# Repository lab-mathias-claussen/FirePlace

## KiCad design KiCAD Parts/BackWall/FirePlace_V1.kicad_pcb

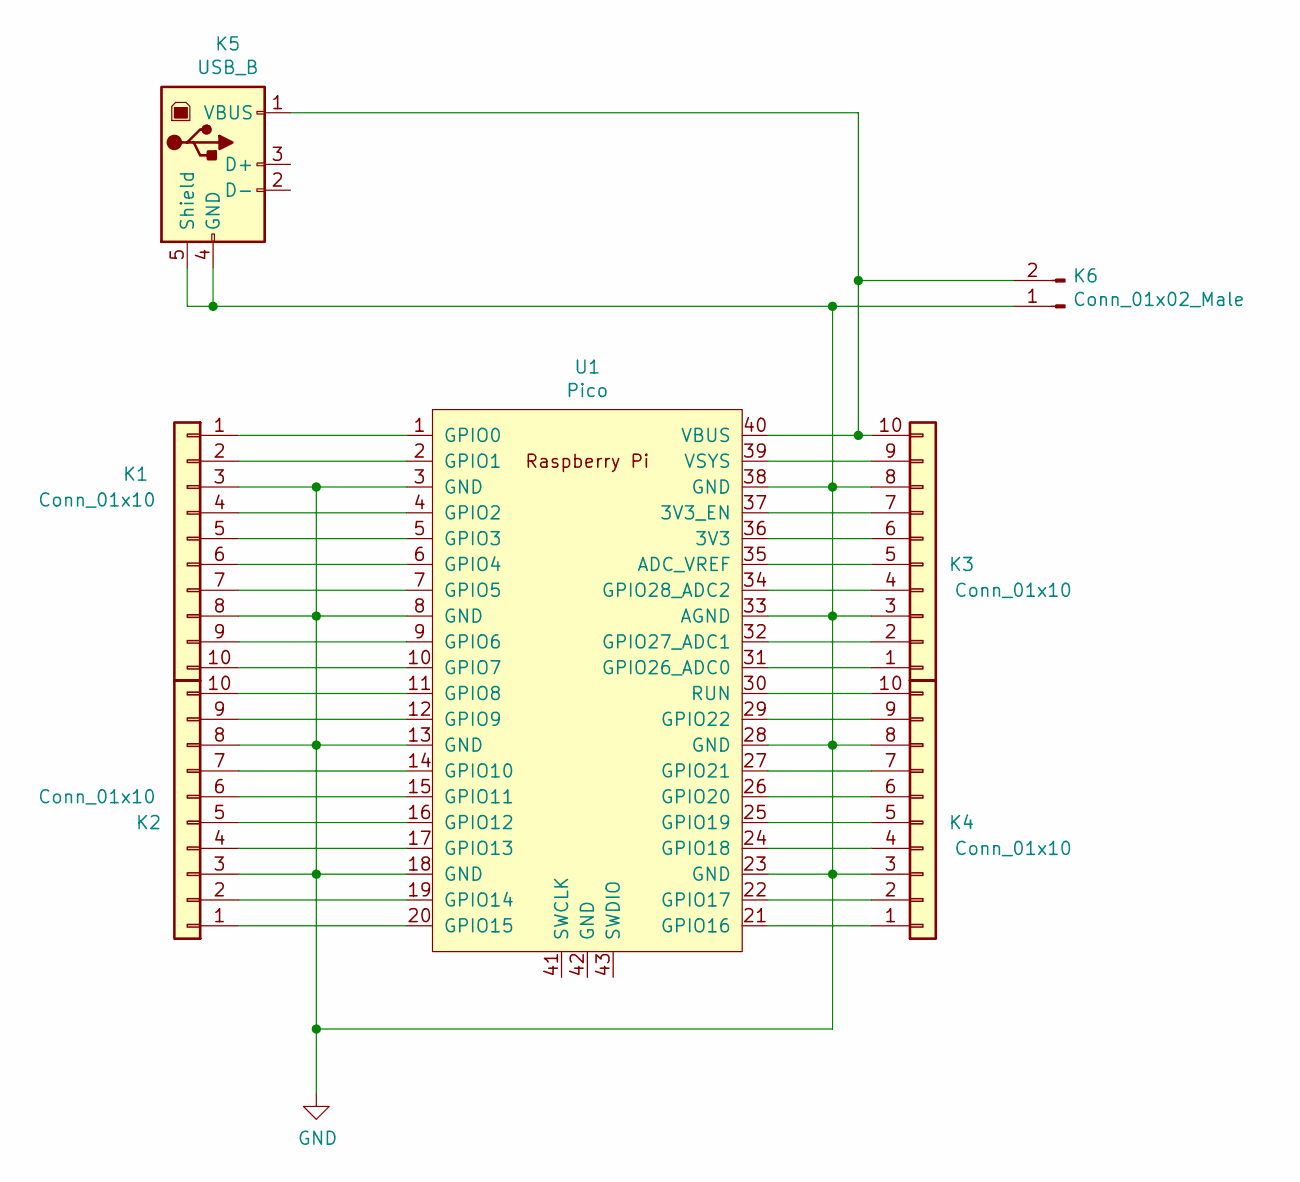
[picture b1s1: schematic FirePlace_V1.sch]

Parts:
K1, K2, K3, K4: Conn_01x10; PinHeader_1x10_P2.54mm_Vertical
K5: USB_B; USB_B_Lumberg_2411_02_Horizontal
K6: Conn_01x02_Male; PinHeader_1x02_P2.54mm_Vertical
U1: Pico; RPi_Pico_SMD_TH

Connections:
GND: K1.3, K1.8, K2.3, K2.8, K3.3, K3.8, K4.3, K4.8, K5.4 (GND), K5.5 (Shield), K6.1, U1.3 (GND), U1.8 (GND), U1.13 (GND), U1.18 (GND), U1.23 (GND), U1.28 (GND), U1.33 (AGND), U1.38 (GND)
unnamed: K1.1, U1.1 (GPIO0)
unnamed: K1.2, U1.2 (GPIO1)
unnamed: K1.4, U1.4 (GPIO2)
unnamed: K1.5, U1.5 (GPIO3)
unnamed: K1.6, U1.6 (GPIO4)
unnamed: K1.7, U1.7 (GPIO5)
unnamed: K1.9, U1.9 (GPIO6)
unnamed: K1.10, U1.10 (GPIO7)
unnamed: K2.1, U1.20 (GPIO15)
unnamed: K2.2, U1.19 (GPIO14)
unnamed: K2.4, U1.17 (GPIO13)
unnamed: K2.5, U1.16 (GPIO12)
unnamed: K2.6, U1.15 (GPIO11)
unnamed: K2.7, U1.14 (GPIO10)
unnamed: K2.9, U1.12 (GPIO9)
unnamed: K2.10, U1.11 (GPIO8)
unnamed: K3.1, U1.31 (GPIO26_ADC0)
unnamed: K3.2, U1.32 (GPIO27_ADC1)
unnamed: K3.4, U1.34 (GPIO28_ADC2)
unnamed: K3.5, U1.35 (ADC_VREF)
unnamed: K3.6, U1.36 (3V3)
unnamed: K3.7, U1.37 (3V3_EN)
unnamed: K3.9, U1.39 (VSYS)
unnamed: K3.10, K5.1 (VBUS), K6.2, U1.40 (VBUS)
unnamed: K4.1, U1.21 (GPIO16)
unnamed: K4.2, U1.22 (GPIO17)
unnamed: K4.4, U1.24 (GPIO18)
unnamed: K4.5, U1.25 (GPIO19)
unnamed: K4.6, U1.26 (GPIO20)
unnamed: K4.7, U1.27 (GPIO21)
unnamed: K4.9, U1.29 (GPIO22)
unnamed: K4.10, U1.30 (RUN)

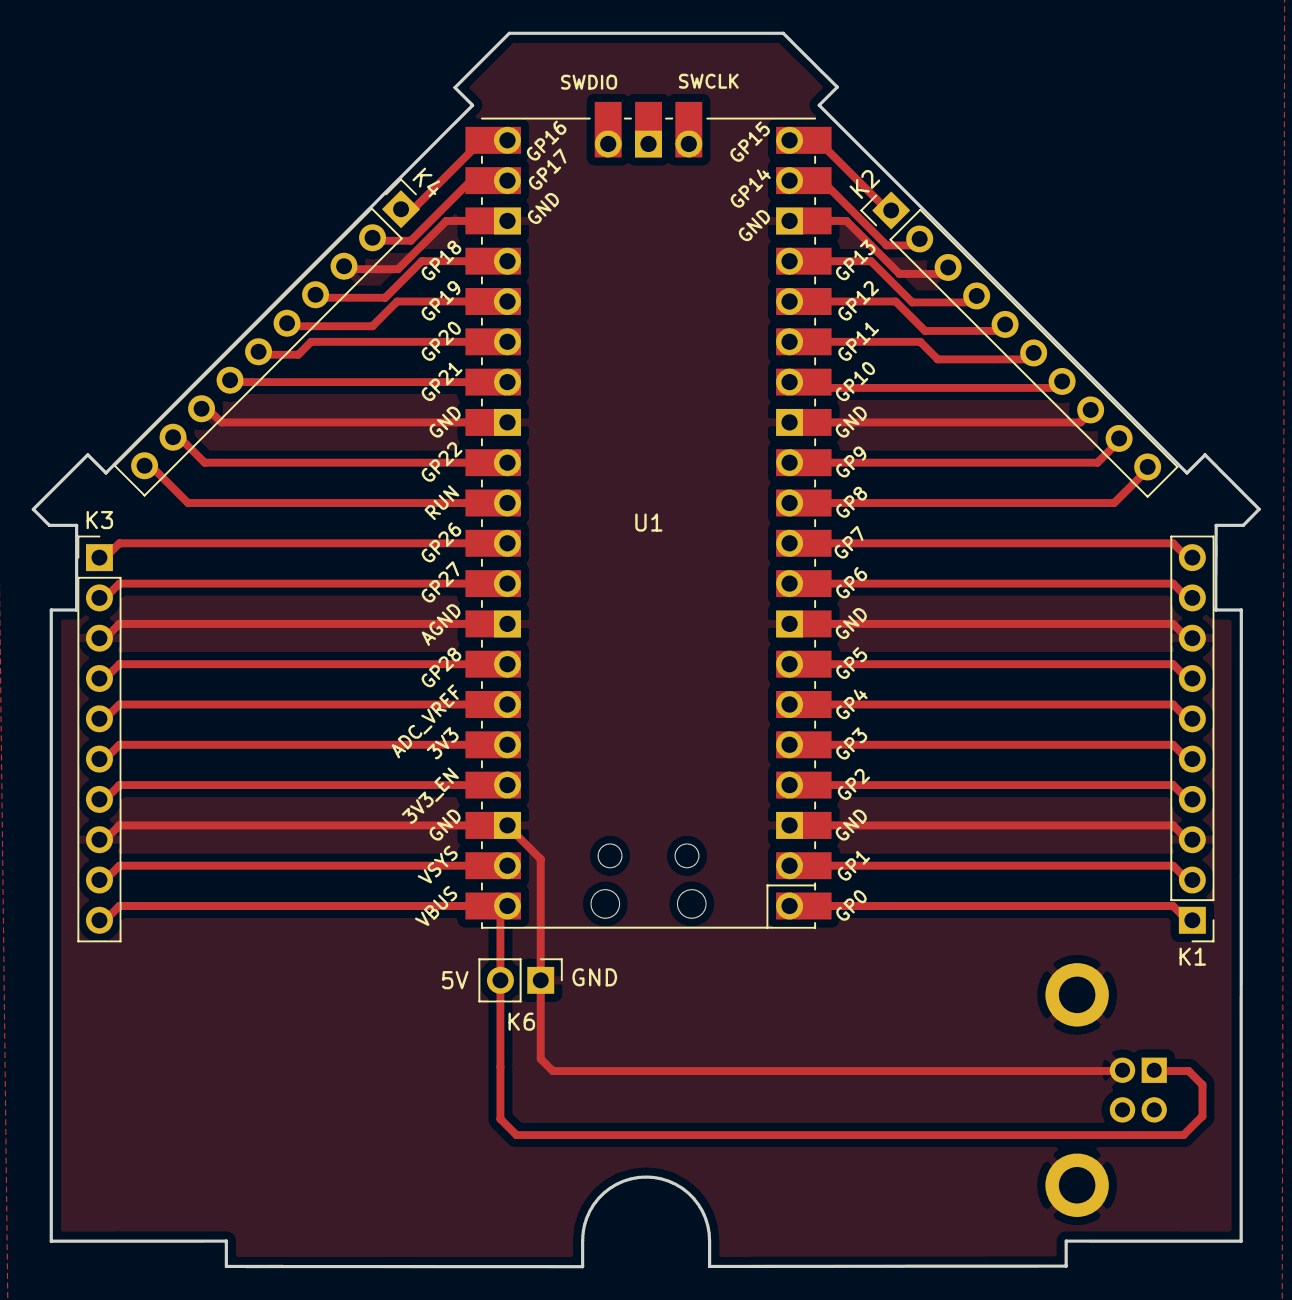
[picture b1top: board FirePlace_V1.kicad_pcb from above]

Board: 2 copper layers, 77.3 x 77.7 mm, 7 parts (1 on the bottom side), 33 nets.

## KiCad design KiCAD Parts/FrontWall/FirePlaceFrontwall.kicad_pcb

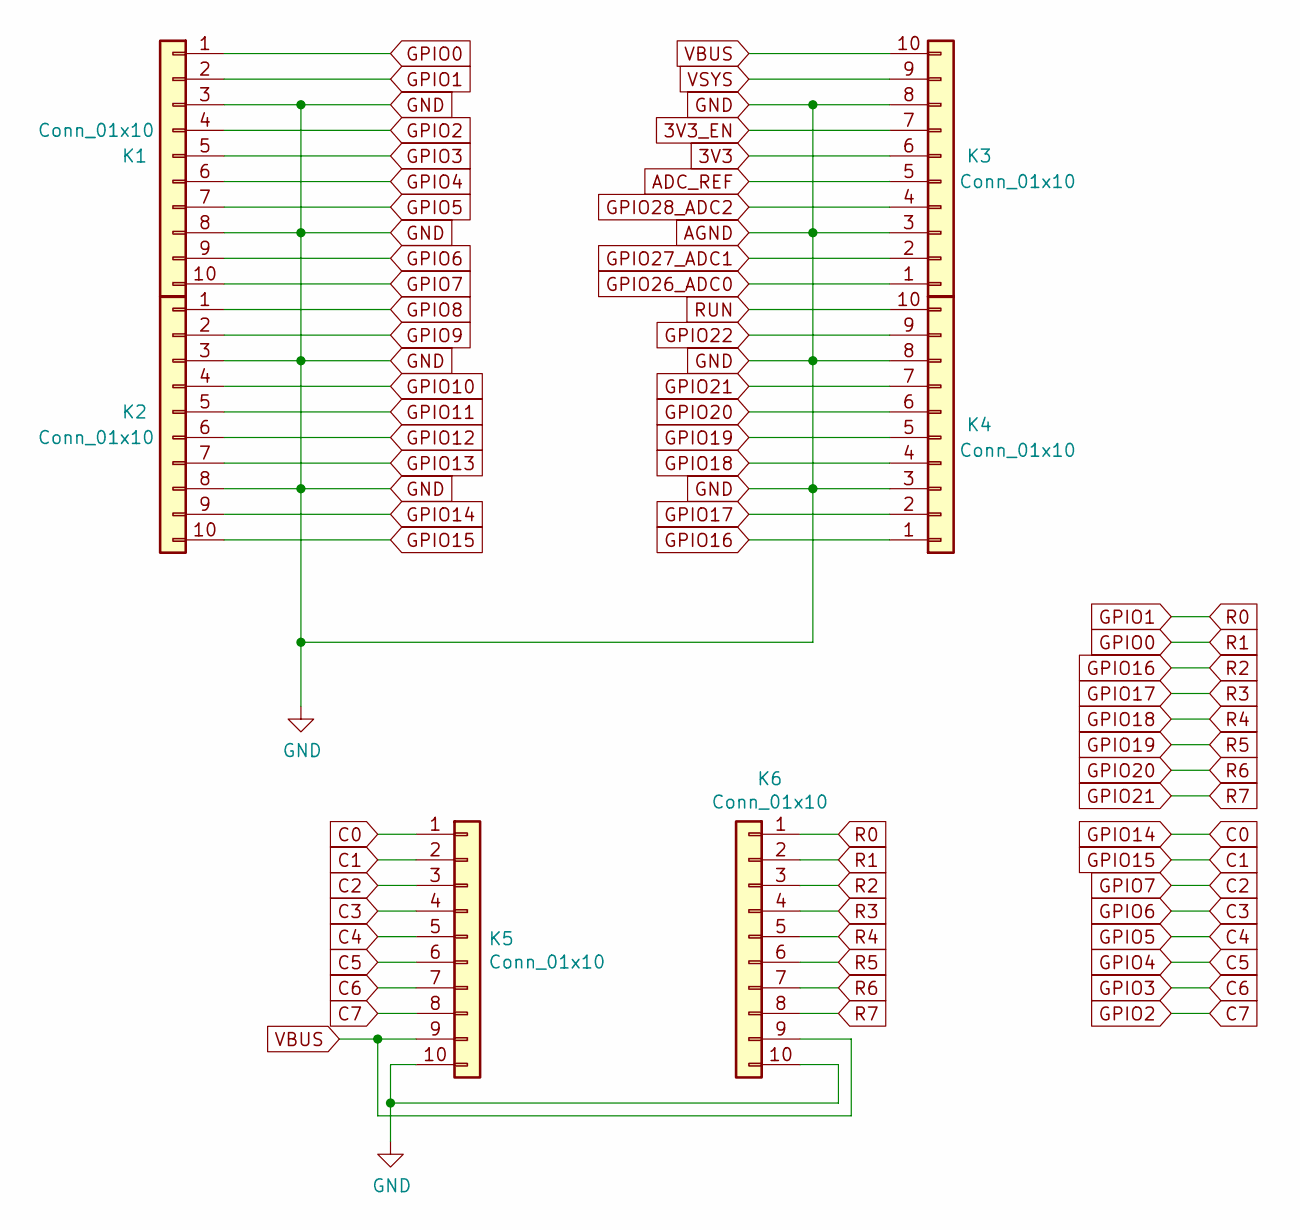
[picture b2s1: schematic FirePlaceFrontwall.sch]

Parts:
K1, K2, K3, K4: Conn_01x10; PinHeader_1x10_P2.54mm_Vertical
K5, K6: Conn_01x10; PinSocket_1x10_P2.54mm_Vertical

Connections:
3V3: K3.6
3V3_EN: K3.7
ADC_REF: K3.5
AGND: K1.3, K1.8, K2.3, K2.8, K3.3, K3.8, K4.3, K4.8, K5.10, K6.10
C0: K2.9, K5.1
C1: K2.10, K5.2
C2: K1.10, K5.3
C3: K1.9, K5.4
C4: K1.7, K5.5
C5: K1.6, K5.6
C6: K1.5, K5.7
C7: K1.4, K5.8
GPIO0: K1.1, K6.2
GPIO1: K1.2, K6.1
GPIO8: K2.1
GPIO9: K2.2
GPIO10: K2.4
GPIO11: K2.5
GPIO12: K2.6
GPIO13: K2.7
GPIO16: K4.1, K6.3
GPIO17: K4.2, K6.4
GPIO18: K4.4, K6.5
GPIO19: K4.5, K6.6
GPIO20: K4.6, K6.7
GPIO21: K4.7, K6.8
GPIO22: K4.9
GPIO26_ADC0: K3.1
GPIO27_ADC1: K3.2
GPIO28_ADC2: K3.4
RUN: K4.10
VBUS: K3.10, K5.9, K6.9
VSYS: K3.9

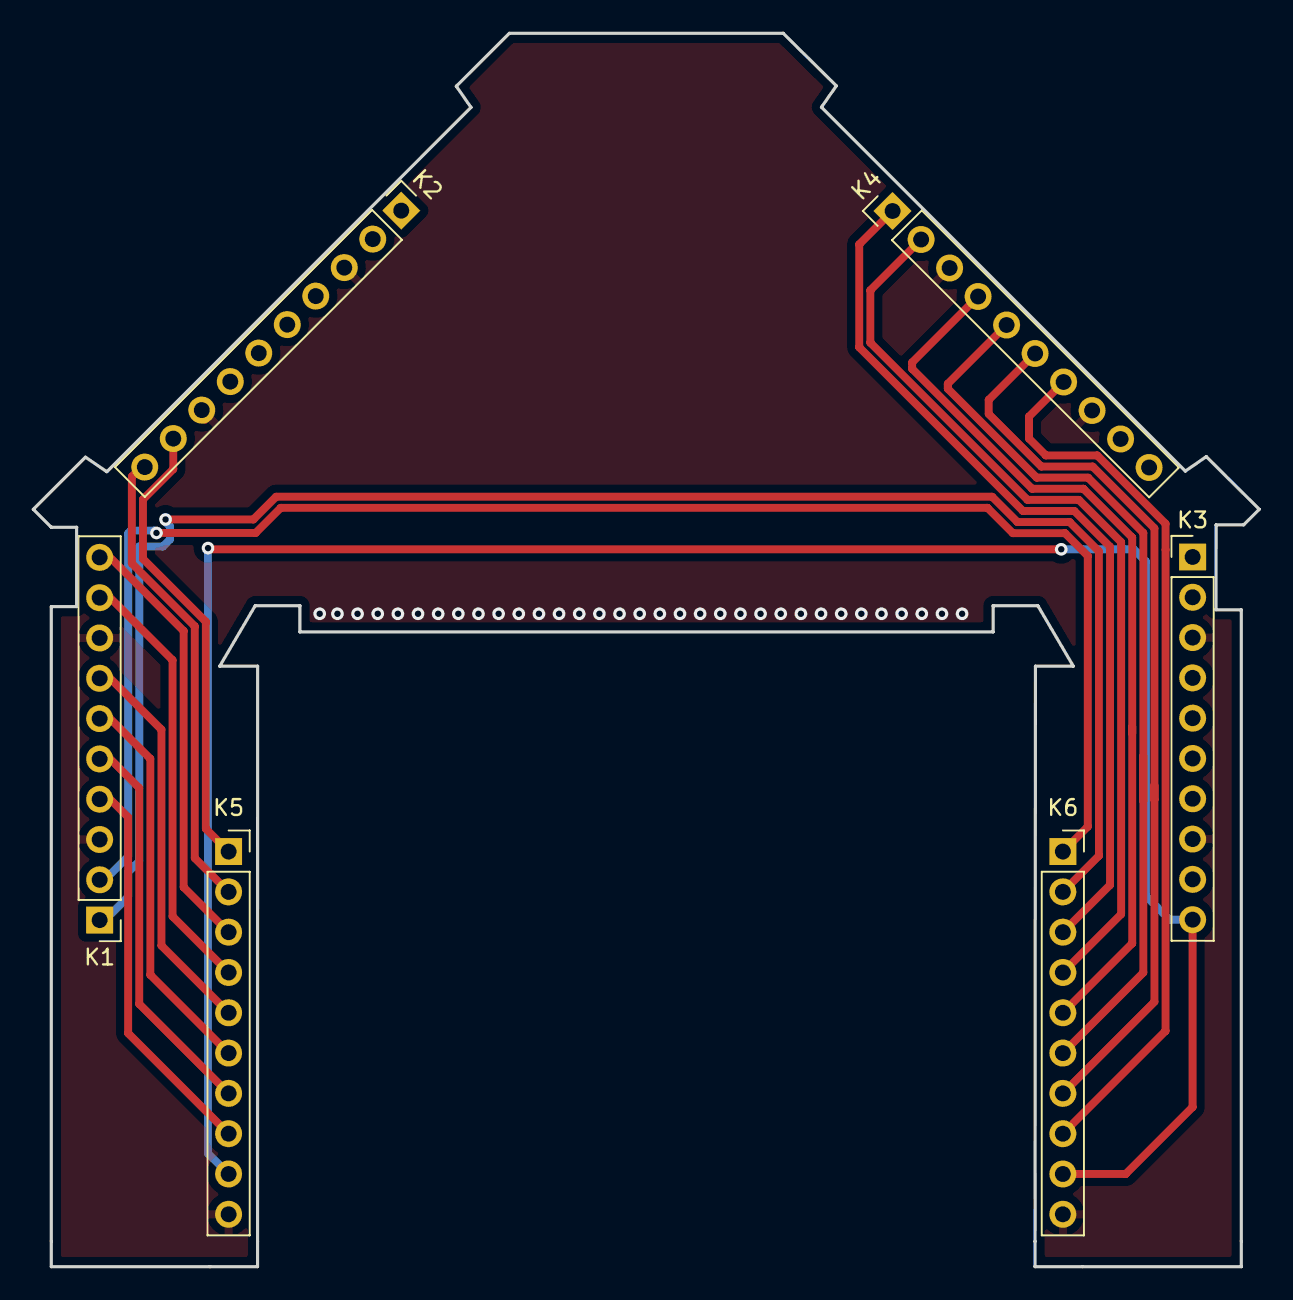
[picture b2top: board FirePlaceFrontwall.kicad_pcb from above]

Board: 2 copper layers, 77.3 x 77.7 mm, 6 parts (0 on the bottom side), 18 nets.

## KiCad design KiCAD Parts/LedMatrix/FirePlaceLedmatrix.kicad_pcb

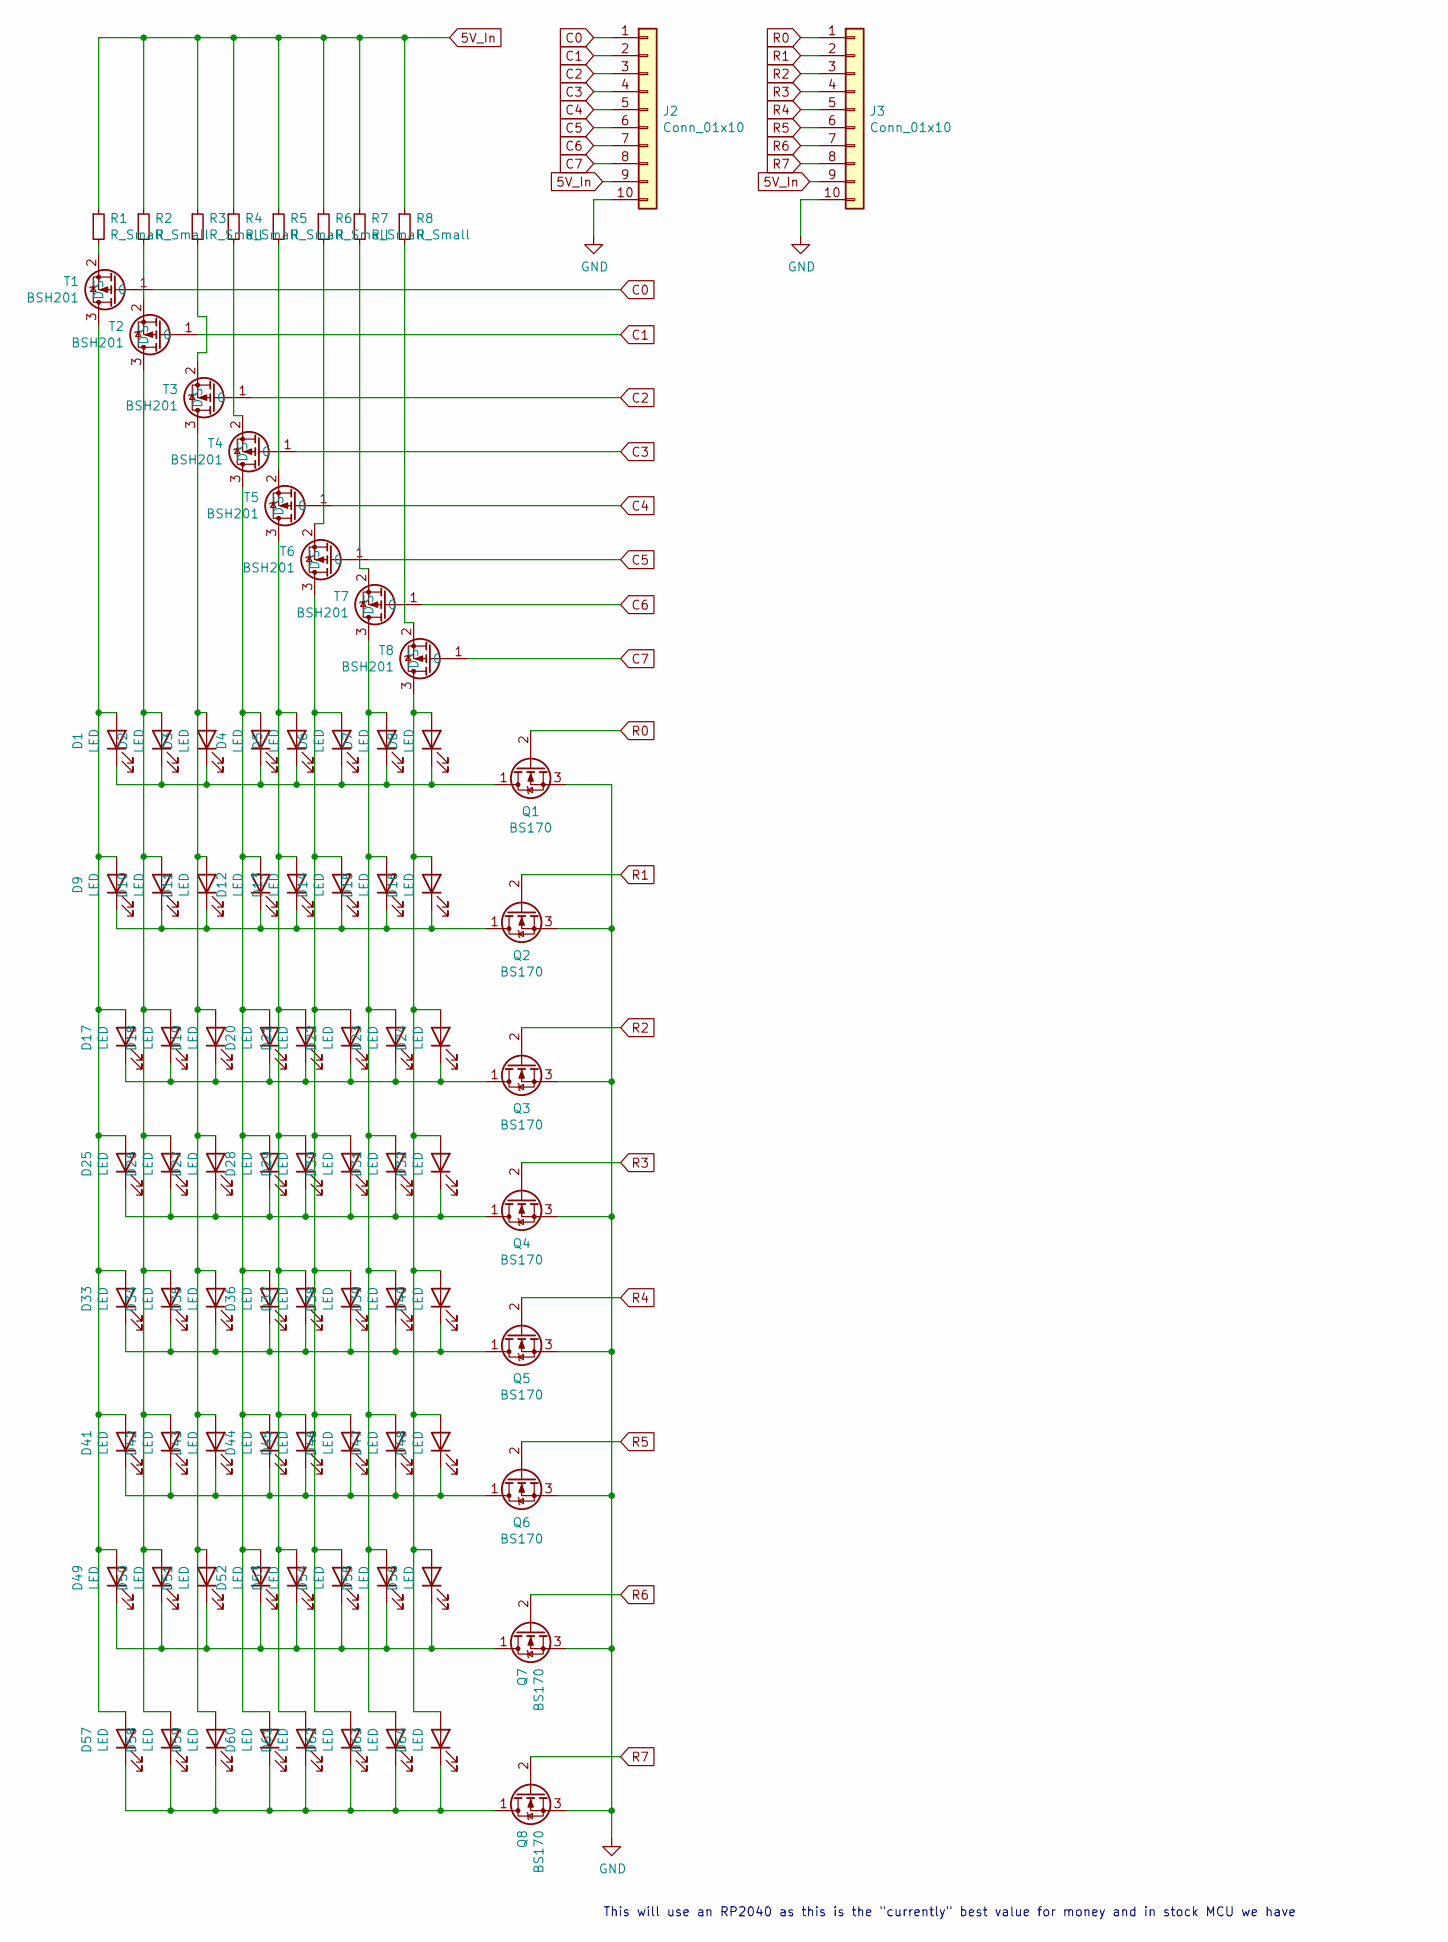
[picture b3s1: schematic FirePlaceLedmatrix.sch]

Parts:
D1, D2, D3, D4, D5, D6, D7, D8, D9, D10, D11, D12, D13, D14, D15, D16, D17, D18, D19, D20, D21, D22, D23, D24, D25, D26, D27, D28, D29, D30, D31, D32, D33, D34, D35, D36, D37, D38, D39, D40, D41, D42, D43, D44, D45, D46, D47, D48, D49, D50, D51, D52, D53, D54, D55, D56, D57, D58, D59, D60, D61, D62, D63, D64: LED; LED_D3.0mm
J2, J3: Conn_01x10; PinHeader_1x10_P2.54mm_Vertical
Q1, Q2, Q3, Q4, Q5, Q6, Q7, Q8: BS170; BS170_SOT23
R1, R2, R3, R4, R5, R6, R7, R8: R_Small; R_0805_2012Metric_Pad1.20x1.40mm_HandSolder
T1, T2, T3, T4, T5, T6, T7, T8: BSH201; SOT-23

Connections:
5V_In: J2.9, J3.9, R1.1, R2.1, R3.1, R4.1, R5.1, R6.1, R7.1, R8.1
C0: J2.1, T1.1 (G)
C1: J2.2, T2.1 (G)
C2: J2.3, T3.1 (G)
C3: J2.4, T4.1 (G)
C4: J2.5, T5.1 (G)
C5: J2.6, T6.1 (G)
C6: J2.7, T7.1 (G)
C7: J2.8, T8.1 (G)
GND: J2.10, J3.10, Q1.3 (S), Q2.3 (S), Q3.3 (S), Q4.3 (S), Q5.3 (S), Q6.3 (S), Q7.3 (S), Q8.3 (S)
unnamed: D1.1 (K), D2.1 (K), D3.1 (K), D4.1 (K), D5.1 (K), D6.1 (K), D7.1 (K), D8.1 (K), Q1.1 (D)
unnamed: D1.2 (A), D9.2 (A), D17.2 (A), D25.2 (A), D33.2 (A), D41.2 (A), D49.2 (A), D57.2 (A), T1.3 (D)
unnamed: D9.1 (K), D10.1 (K), D11.1 (K), D12.1 (K), D13.1 (K), D14.1 (K), D15.1 (K), D16.1 (K), Q2.1 (D)
unnamed: D2.2 (A), D10.2 (A), D18.2 (A), D26.2 (A), D34.2 (A), D42.2 (A), D50.2 (A), D58.2 (A), T2.3 (D)
unnamed: D3.2 (A), D11.2 (A), D19.2 (A), D27.2 (A), D35.2 (A), D43.2 (A), D51.2 (A), D59.2 (A), T3.3 (D)
unnamed: D4.2 (A), D12.2 (A), D20.2 (A), D28.2 (A), D36.2 (A), D44.2 (A), D52.2 (A), D60.2 (A), T4.3 (D)
unnamed: D5.2 (A), D13.2 (A), D21.2 (A), D29.2 (A), D37.2 (A), D45.2 (A), D53.2 (A), D61.2 (A), T5.3 (D)
unnamed: D6.2 (A), D14.2 (A), D22.2 (A), D30.2 (A), D38.2 (A), D46.2 (A), D54.2 (A), D62.2 (A), T6.3 (D)
unnamed: D7.2 (A), D15.2 (A), D23.2 (A), D31.2 (A), D39.2 (A), D47.2 (A), D55.2 (A), D63.2 (A), T7.3 (D)
unnamed: D8.2 (A), D16.2 (A), D24.2 (A), D32.2 (A), D40.2 (A), D48.2 (A), D56.2 (A), D64.2 (A), T8.3 (D)
unnamed: D17.1 (K), D18.1 (K), D19.1 (K), D20.1 (K), D21.1 (K), D22.1 (K), D23.1 (K), D24.1 (K), Q3.1 (D)
unnamed: D25.1 (K), D26.1 (K), D27.1 (K), D28.1 (K), D29.1 (K), D30.1 (K), D31.1 (K), D32.1 (K), Q4.1 (D)
unnamed: D33.1 (K), D34.1 (K), D35.1 (K), D36.1 (K), D37.1 (K), D38.1 (K), D39.1 (K), D40.1 (K), Q5.1 (D)
unnamed: D41.1 (K), D42.1 (K), D43.1 (K), D44.1 (K), D45.1 (K), D46.1 (K), D47.1 (K), D48.1 (K), Q6.1 (D)
unnamed: D49.1 (K), D50.1 (K), D51.1 (K), D52.1 (K), D53.1 (K), D54.1 (K), D55.1 (K), D56.1 (K), Q7.1 (D)
unnamed: D57.1 (K), D58.1 (K), D59.1 (K), D60.1 (K), D61.1 (K), D62.1 (K), D63.1 (K), D64.1 (K), Q8.1 (D)
unnamed: R1.2, T1.2 (S)
unnamed: R2.2, T2.2 (S)
unnamed: R3.2, T3.2 (S)
unnamed: R4.2, T4.2 (S)
unnamed: R5.2, T5.2 (S)
unnamed: R6.2, T6.2 (S)
unnamed: R7.2, T7.2 (S)
unnamed: R8.2, T8.2 (S)
R0: J3.1, Q1.2 (G)
R1: J3.2, Q2.2 (G)
R2: J3.3, Q3.2 (G)
R3: J3.4, Q4.2 (G)
R4: J3.5, Q5.2 (G)
R5: J3.6, Q6.2 (G)
R6: J3.7, Q7.2 (G)
R7: J3.8, Q8.2 (G)

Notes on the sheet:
This will use an RP2040 as this is the "currently" best value for money and in stock MCU we have

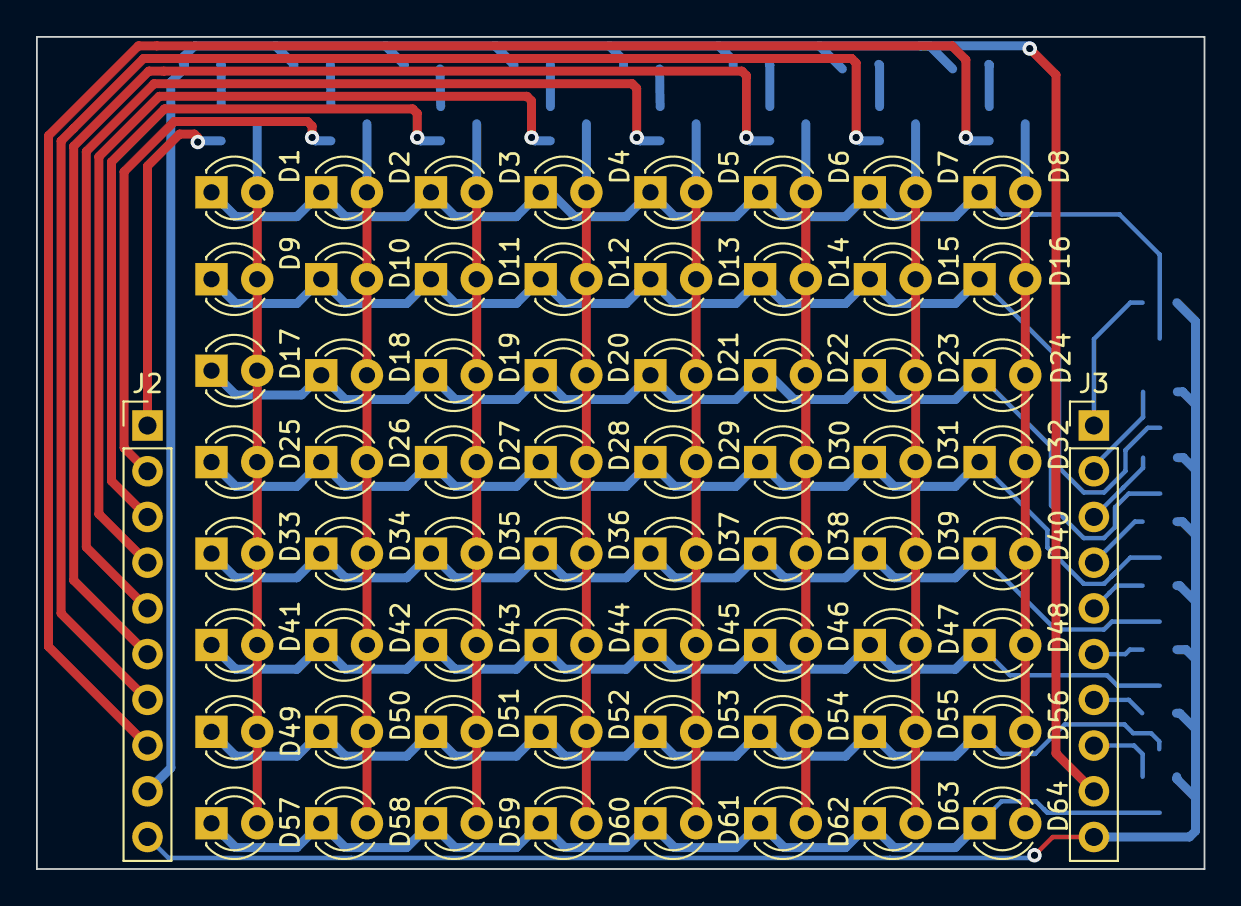
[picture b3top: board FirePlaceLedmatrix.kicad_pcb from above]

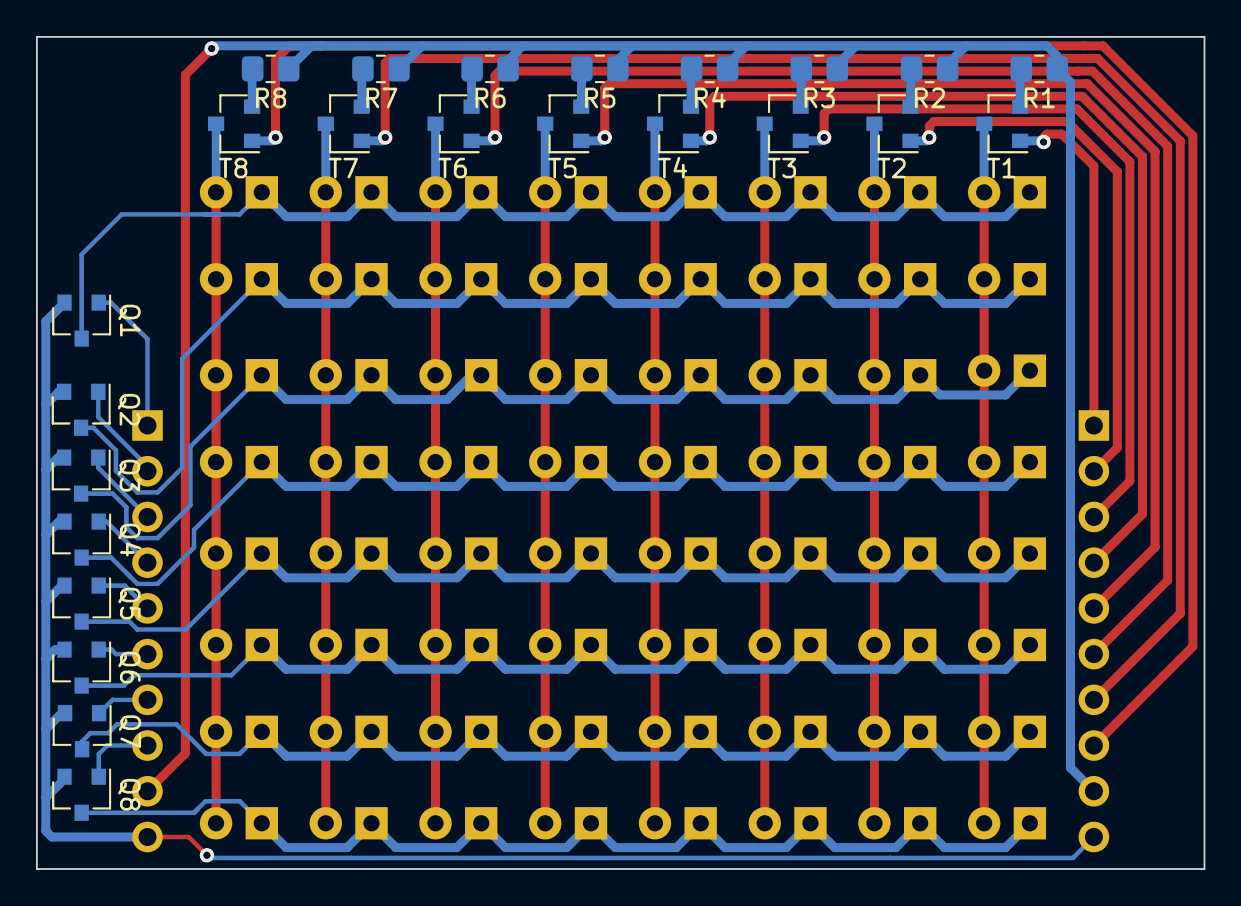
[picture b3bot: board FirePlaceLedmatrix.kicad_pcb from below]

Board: 2 copper layers, 64.9 x 46.2 mm, 90 parts (24 on the bottom side), 42 nets.

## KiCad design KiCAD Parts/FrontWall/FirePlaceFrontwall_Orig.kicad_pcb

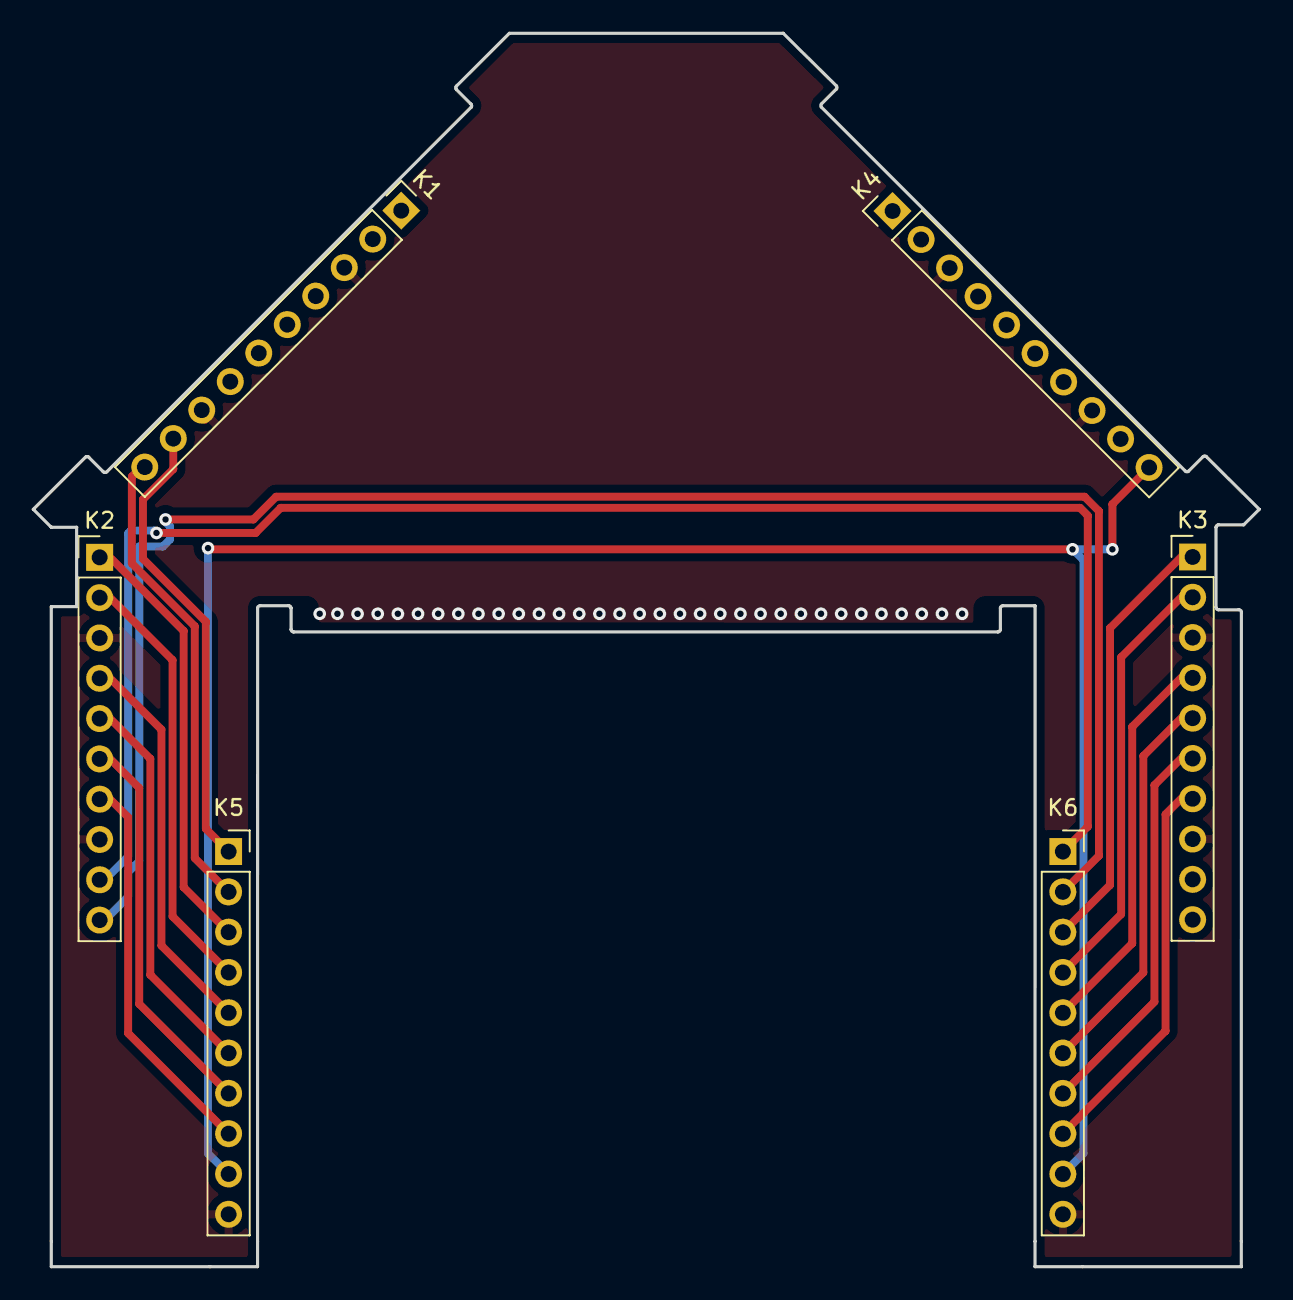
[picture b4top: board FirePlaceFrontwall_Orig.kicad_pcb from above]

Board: 2 copper layers, 77.3 x 77.7 mm, 6 parts (0 on the bottom side), 18 nets.

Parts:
K1, K2, K3, K4: Conn_01x10; PinHeader_1x10_P2.54mm_Vertical
K5, K6: Conn_01x10; PinSocket_1x10_P2.54mm_Vertical

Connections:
AGND: K1.3, K1.8, K2.3, K2.8, K3.3, K3.8, K4.3, K4.8, K5.10, K6.10
C0: K1.9, K5.1
C1: K1.10, K5.2
C2: K2.1, K5.3
C3: K2.2, K5.4
C4: K2.4, K5.5
C5: K2.5, K5.6
C6: K2.6, K5.7
C7: K2.7, K5.8
GPIO14: K2.9, K6.1
GPIO15: K2.10, K6.2
GPIO16: K3.1, K6.3
GPIO17: K3.2, K6.4
GPIO18: K3.4, K6.5
GPIO19: K3.5, K6.6
GPIO20: K3.6, K6.7
GPIO21: K3.7, K6.8
VBUS: K4.10, K5.9, K6.9

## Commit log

2021-12-13 Added Arduino code
    Added Arduino code for the led matrix
2021-12-13 Added images
    Images for refference added
2021-12-14 Added binary as U2F for direct upload
    Precompiled U2F File added for Upload RP Pico
